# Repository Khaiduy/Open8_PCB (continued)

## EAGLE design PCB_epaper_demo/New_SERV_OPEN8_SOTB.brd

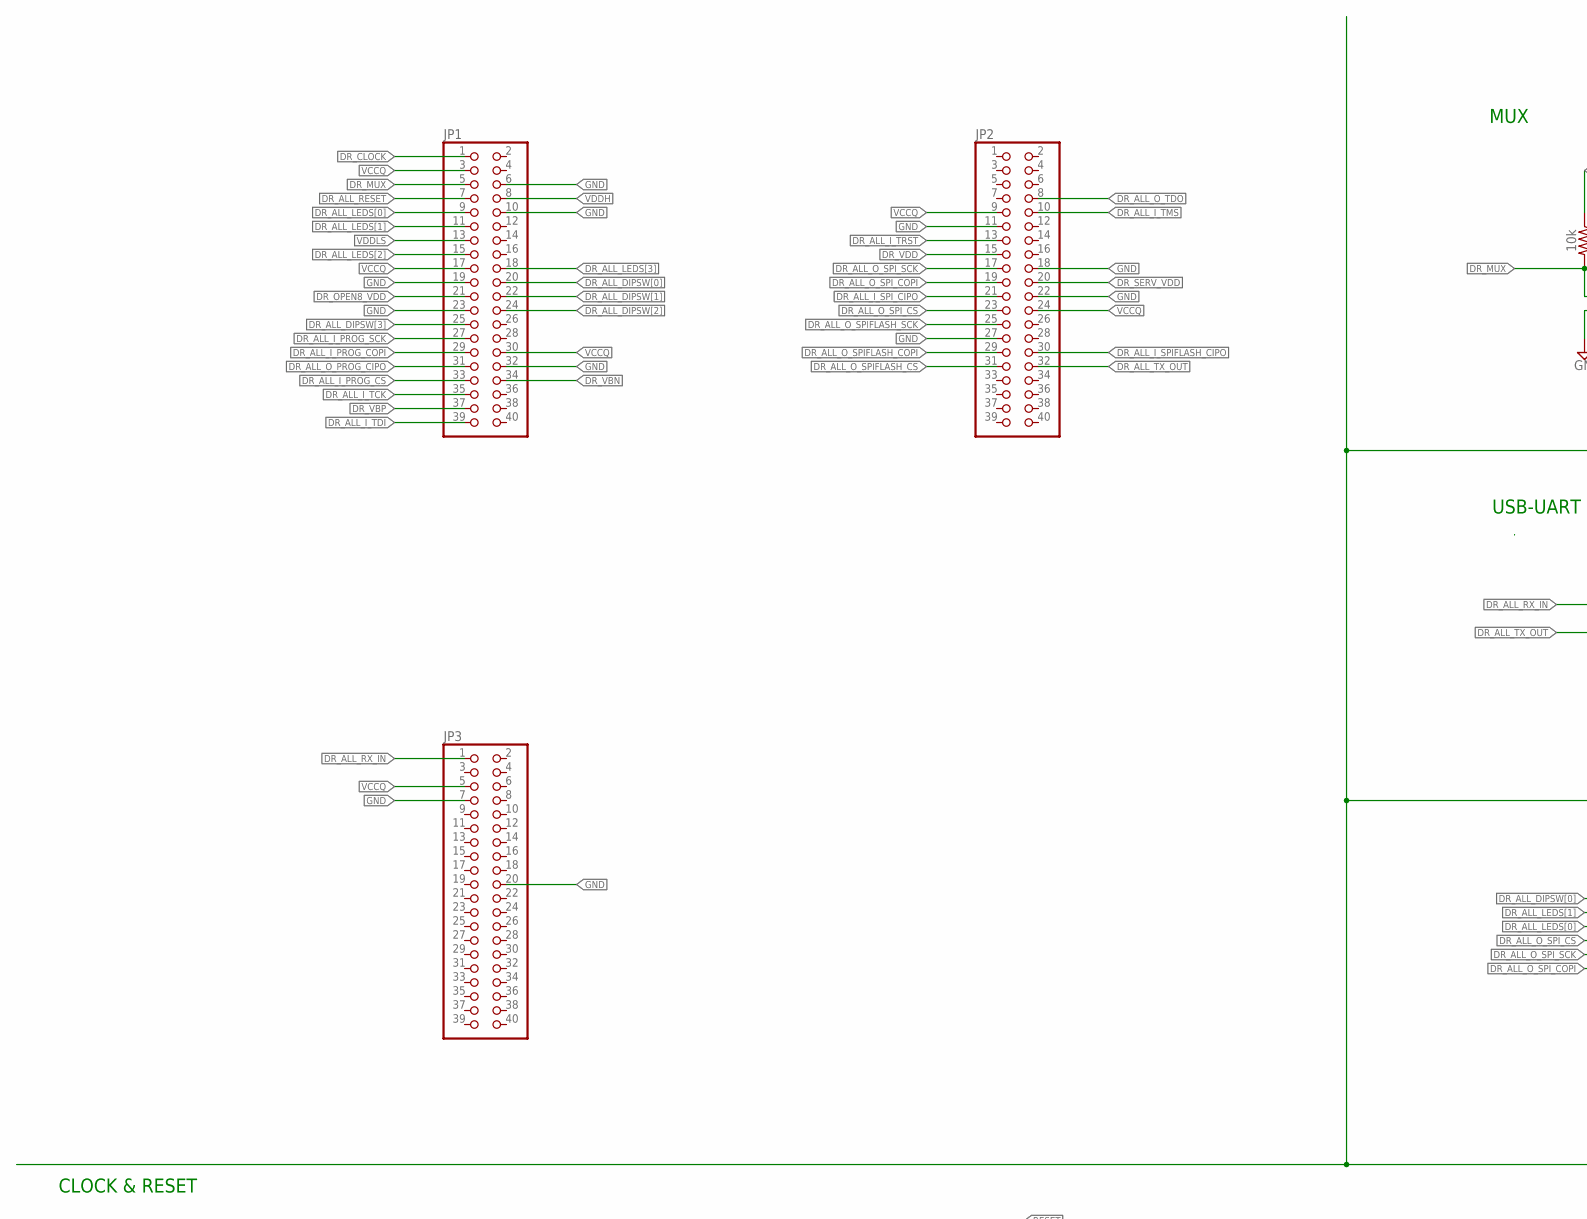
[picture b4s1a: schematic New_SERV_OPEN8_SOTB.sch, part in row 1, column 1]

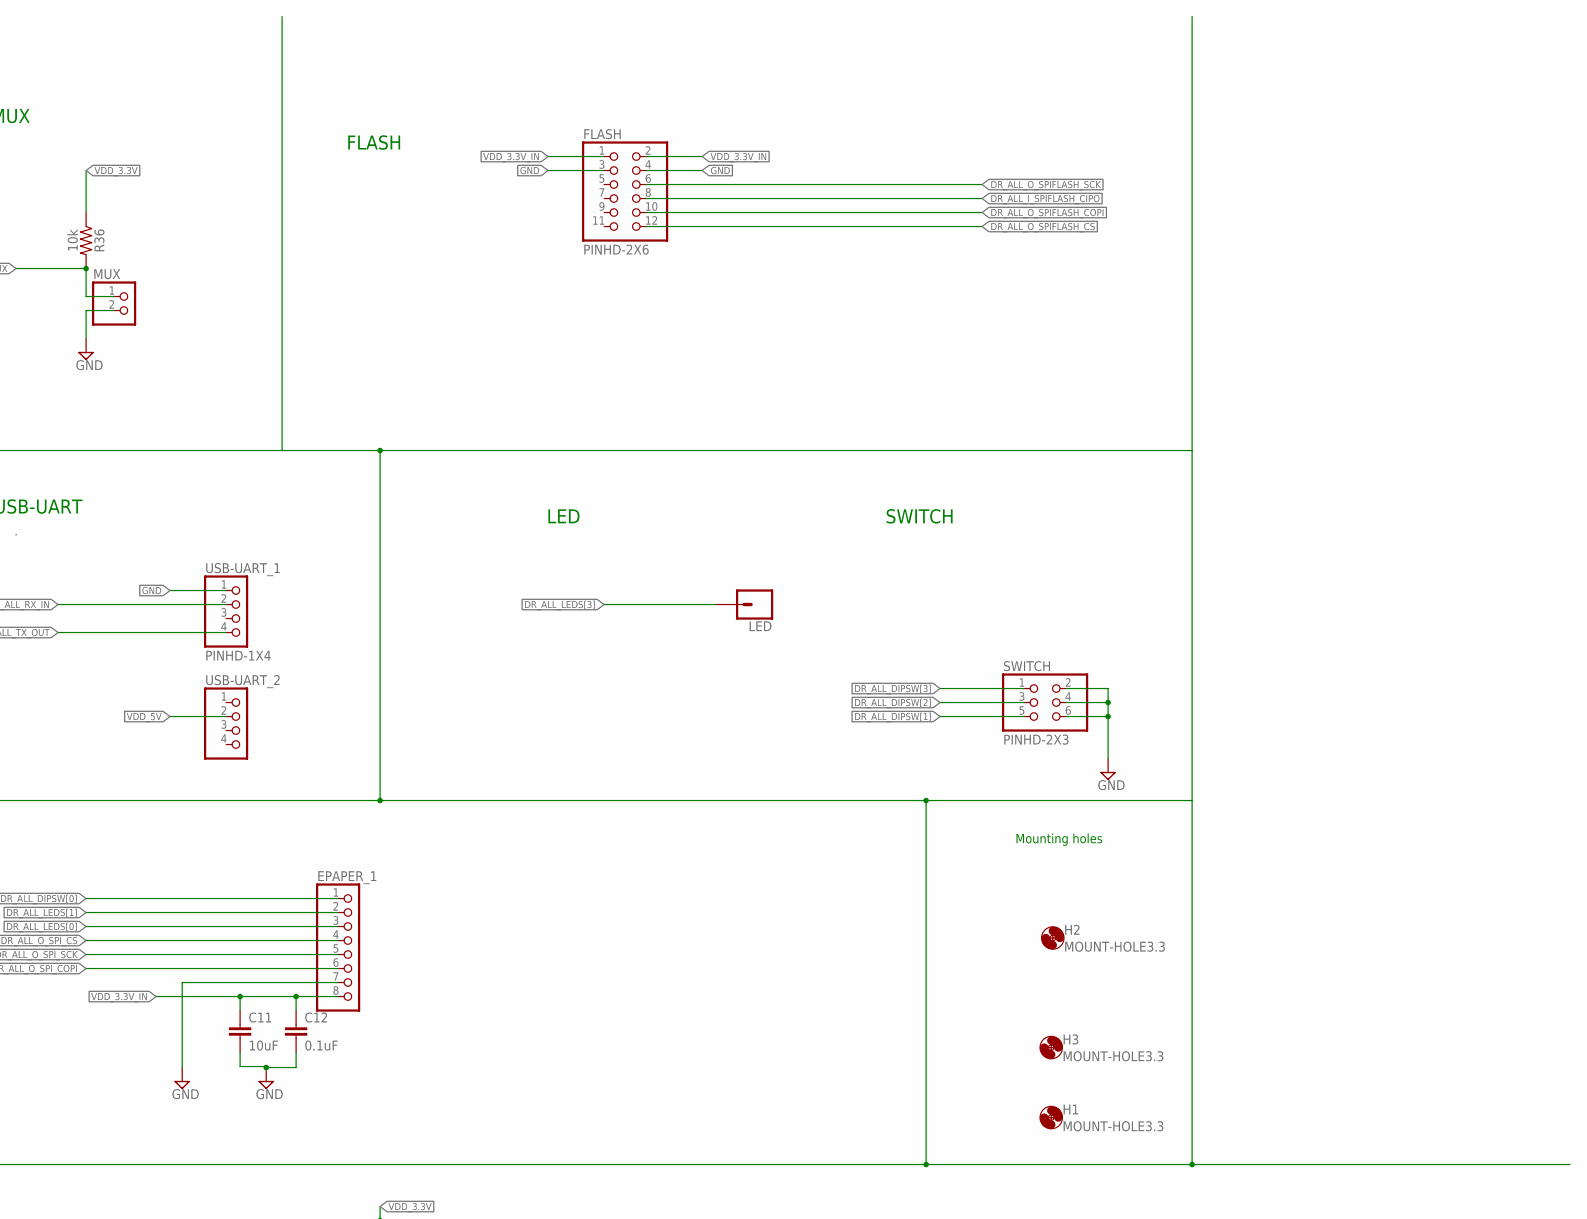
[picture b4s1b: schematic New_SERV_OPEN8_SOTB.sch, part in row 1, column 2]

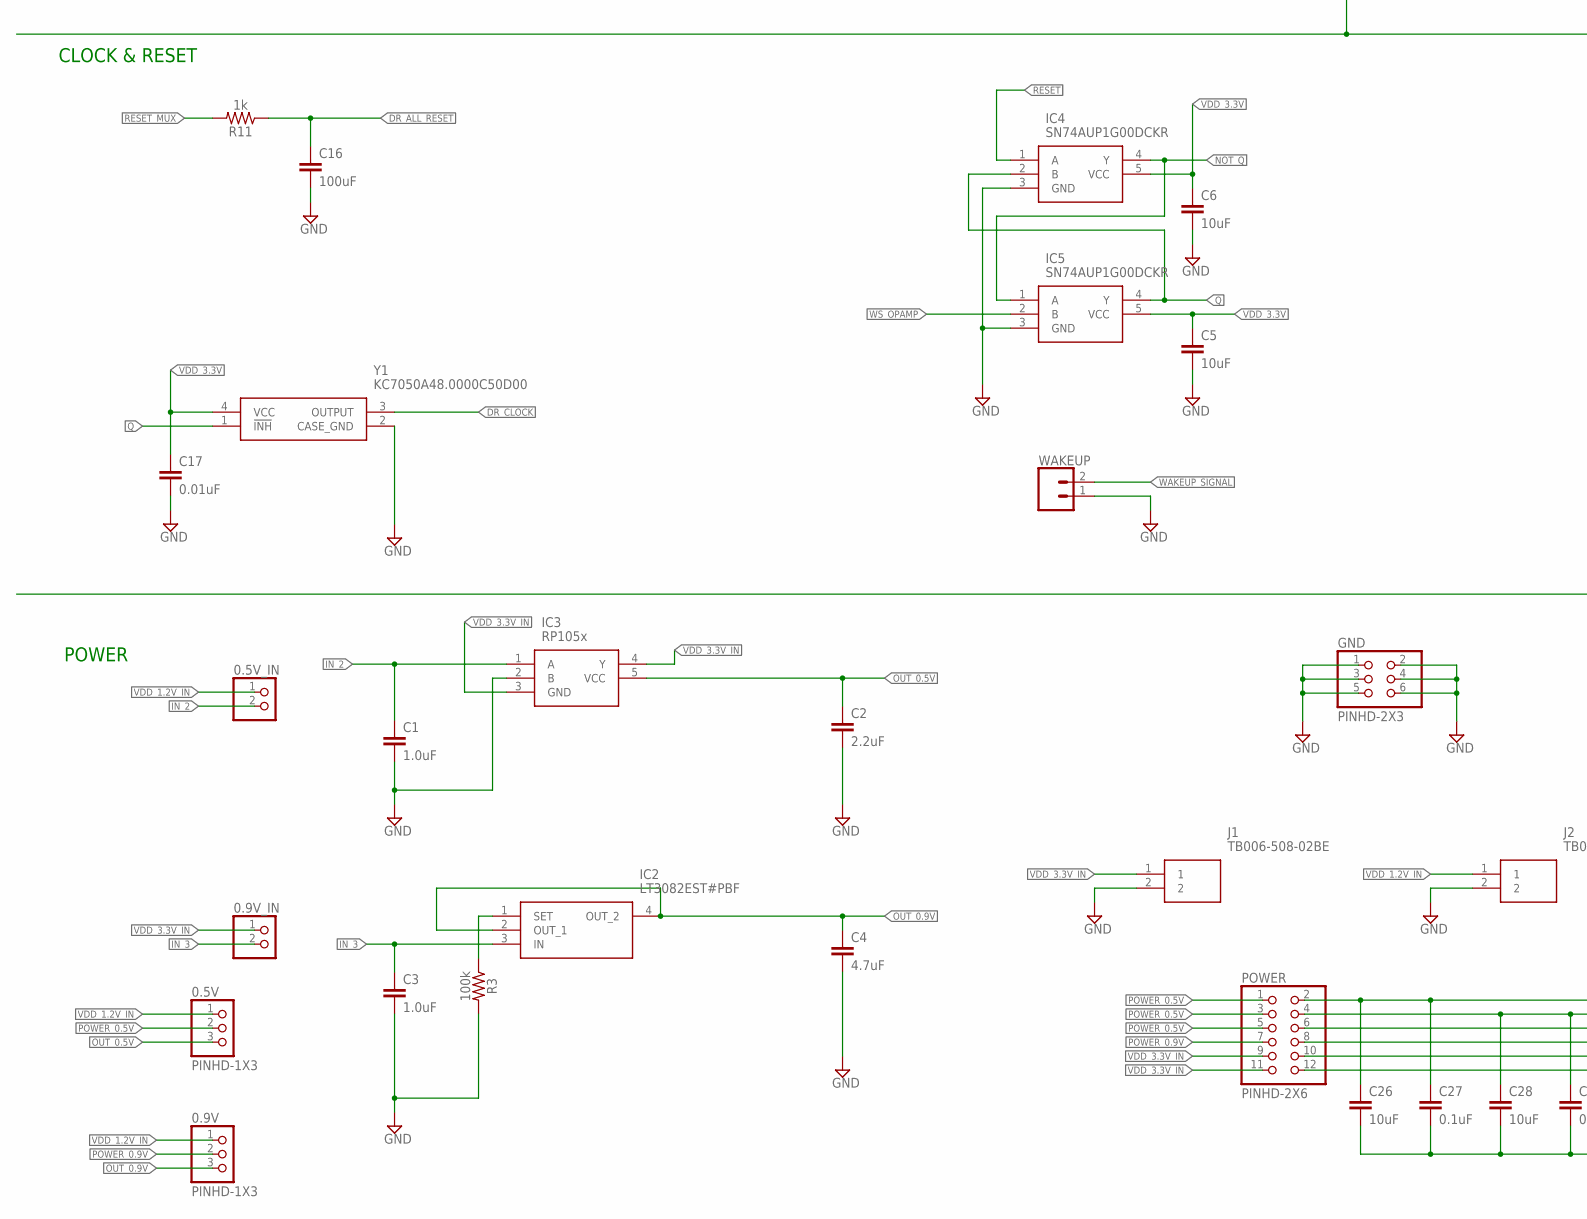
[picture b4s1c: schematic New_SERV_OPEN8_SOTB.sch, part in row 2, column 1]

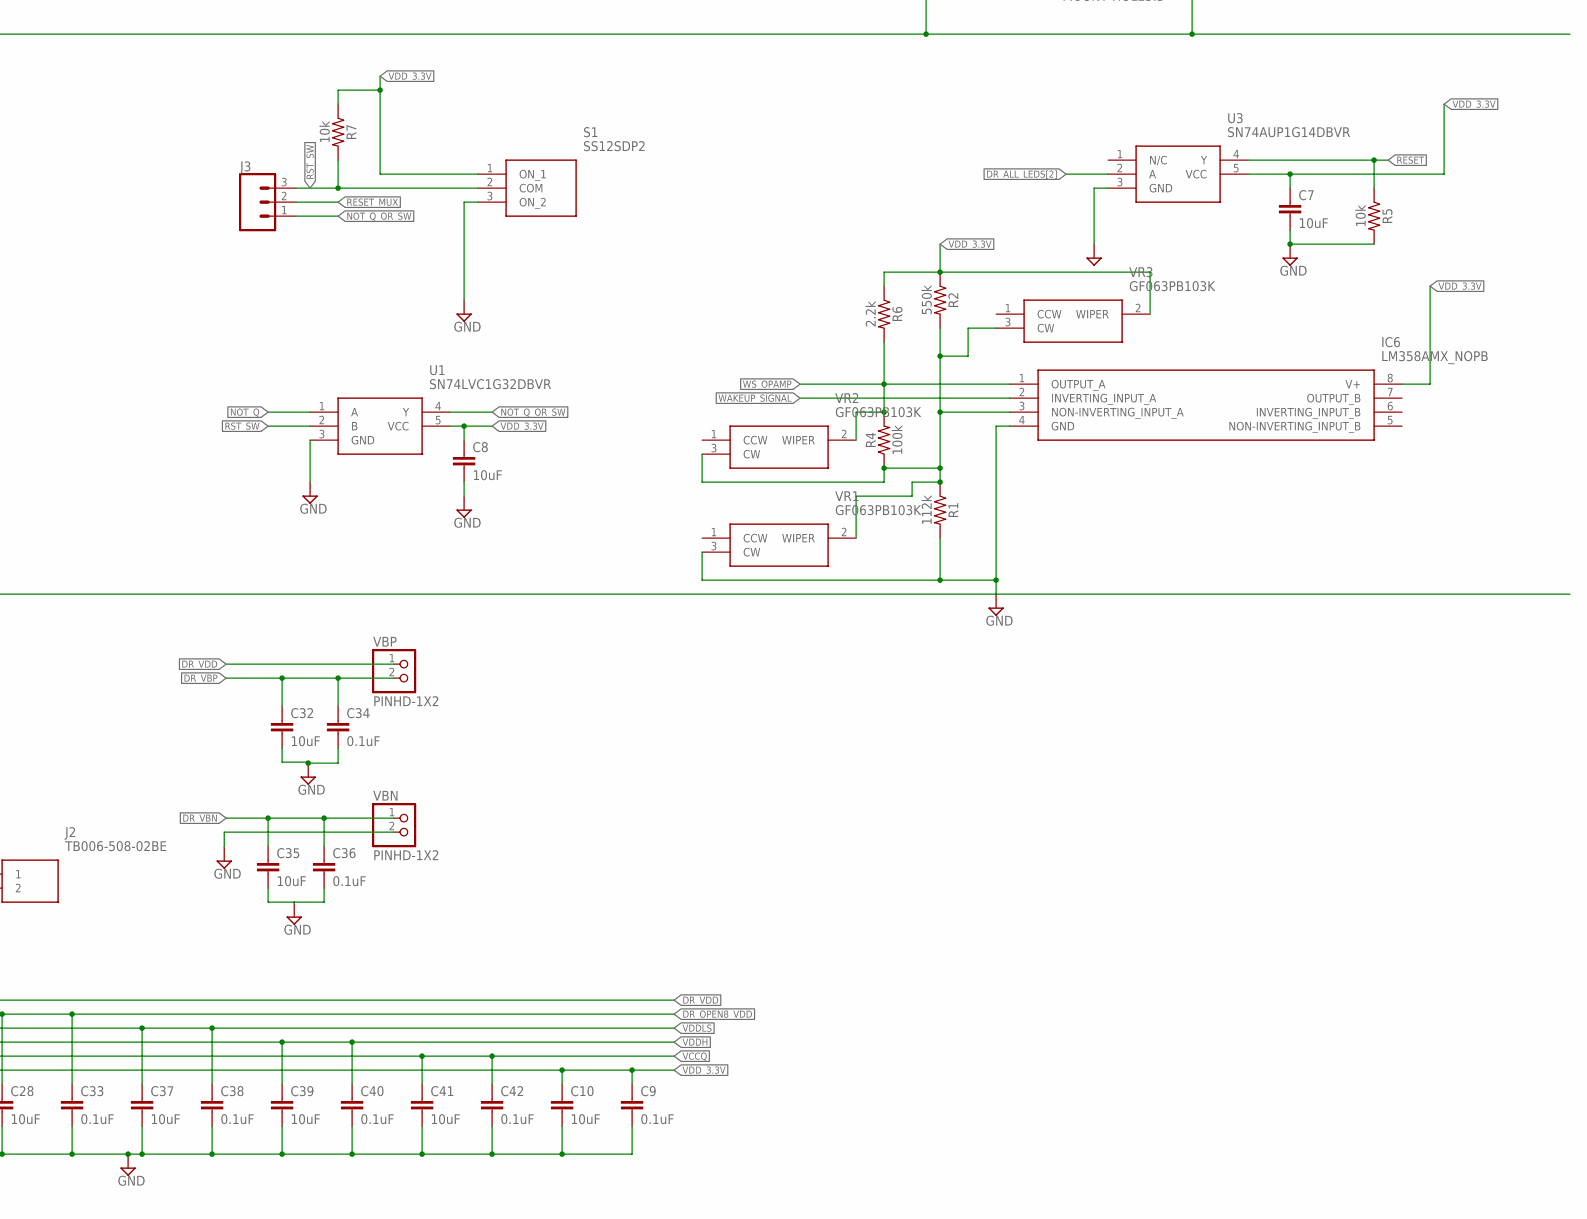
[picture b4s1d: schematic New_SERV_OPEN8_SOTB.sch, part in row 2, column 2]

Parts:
0.5V, 0.9V: PINHD-1X3; 1X03
0.5V_IN, 0.9V_IN: PINHD-1X2; 1X02
C1, C3: 1.0uF; 0805
C2: 2.2uF; 0805
C4: 4.7uF; 0805
C5, C6, C7, C8, C10, C11, C26, C28, C32, C35, C37, C39, C41: 10uF; 0805
C9, C12, C27, C33, C34, C36, C38, C40, C42: 0.1uF; 0805
C16: 100uF; 0805
C17: 0.01uF; 0805
EPAPER_1: PINHD-1X8; 1X08
FLASH: PINHD-2X6; 2X06
GND: PINHD-2X3; 2X03
H1, H2, H3: MOUNT-HOLE3.3; 3,3
IC2: LT3082EST#PBF; SOT230P700X180-4N
IC3: RP105x; SOT95P280X145-5N
IC4, IC5: SN74AUP1G00DCKR; SOT65P210X110-5N
IC6: LM358AMX_NOPB; SOIC127P600X175-8N
J1, J2: TB006-508-02BE; TB00650802BE
J3: CONN_03; 1X03
JP1, JP2, JP3: PINHD-2X20; 2X20
LED: CONN_01; 1X01
MUX: PINHD-1X2; 1X02
POWER: PINHD-2X6; 2X06
R1: 112k; 0805
R2: 550k; 0805
R3, R4: 100k; 0805
R5, R7, R36: 10k; 0805
R6: 2.2k; 0805
R11: 1k; 0805
S1: SS12SDP2
SWITCH: PINHD-2X3; 2X03
U1: SN74LVC1G32DBVR; SOT95P280X145-5N
U3: SN74AUP1G14DBVR; SOT65P210X110-5N
USB-UART_1, USB-UART_2: PINHD-1X4; 1X04
VBN: PINHD-1X2; 1X02
VBP: PINHD-1X2; 1X02
VR1, VR2, VR3: GF063PB103K
WAKEUP: CONN_02; 1X02
Y1: KC7050A48.0000C50D00; KC7050A480000C50D00

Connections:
DR_ALL_DIPSW[0]: EPAPER_1.1, JP1.20
DR_ALL_DIPSW[1]: JP1.22, SWITCH.5
DR_ALL_DIPSW[2]: JP1.24, SWITCH.3
DR_ALL_DIPSW[3]: JP1.25, SWITCH.1
DR_ALL_I_PROG_COPI: JP1.29
DR_ALL_I_PROG_CS: JP1.33
DR_ALL_I_PROG_SCK: JP1.27
DR_ALL_I_SPIFLASH_CIPO: FLASH.8, JP2.30
DR_ALL_I_SPI_CIPO: JP2.21
DR_ALL_I_TCK: JP1.35
DR_ALL_I_TDI: JP1.39
DR_ALL_I_TMS: JP2.10
DR_ALL_I_TRST: JP2.13
DR_ALL_LEDS[0]: EPAPER_1.3, JP1.9
DR_ALL_LEDS[1]: EPAPER_1.2, JP1.11
DR_ALL_LEDS[2]: JP1.15, U3.2 (A)
DR_ALL_LEDS[3]: JP1.18, LED.1
DR_ALL_O_PROG_CIPO: JP1.31
DR_ALL_O_SPIFLASH_COPI: FLASH.10, JP2.29
DR_ALL_O_SPIFLASH_CS: FLASH.12, JP2.31
DR_ALL_O_SPIFLASH_SCK: FLASH.6, JP2.25
DR_ALL_O_SPI_COPI: EPAPER_1.6, JP2.19
DR_ALL_O_SPI_CS: EPAPER_1.4, JP2.23
DR_ALL_O_SPI_SCK: EPAPER_1.5, JP2.17
DR_ALL_O_TDO: JP2.8
DR_ALL_RESET: C16.1, JP1.7, R11.1
DR_ALL_RX_IN: JP3.1, USB-UART_1.2
DR_ALL_TX_OUT: JP2.32, USB-UART_1.4
DR_CLOCK: JP1.1, Y1.3 (OUTPUT)
DR_MUX: JP1.5, MUX.1, R36.2
DR_OPEN8_VDD: C28.1, C33.1, JP1.21, POWER.4
DR_SERV_VDD: JP2.20
DR_VBN: C35.1, C36.1, JP1.34, VBN.1
DR_VBP: C32.1, C34.1, JP1.37, VBP.2
DR_VDD: C26.1, C27.1, JP2.15, POWER.2, VBP.1
GND: C1.2, C2.2, C3.2, C4.2, C5.2, C6.2, C7.2, C8.2, C9.2, C10.2, C11.2, C12.2, C16.2, C17.2, C26.2, C27.2, C28.2, C32.2, C33.2, C34.2, C35.2, C36.2, C37.2, C38.2, C39.2, C40.2, C41.2, C42.2, EPAPER_1.7, FLASH.3, FLASH.4, GND.1, GND.2, GND.3, GND.4, GND.5, GND.6, IC3.2 (B), IC4.3 (GND), IC5.3 (GND), IC6.4 (GND), J1.2, J2.2, JP1.6, JP1.10, JP1.19, JP1.23, JP1.32, JP2.11, JP2.18, JP2.22, JP2.27, JP3.7, JP3.20, MUX.2, R1.2, R3.2, R5.2, S1.3 (ON_2), SWITCH.2, SWITCH.4, SWITCH.6, U1.3 (GND), U3.3 (GND), USB-UART_1.1, VBN.2, VR1.3 (CW), WAKEUP.1, Y1.2 (CASE_GND)
IN_2: 0.5V_IN.2, C1.1, IC3.1 (A)
IN_3: 0.9V_IN.2, C3.1, IC2.3 (IN)
unnamed: IC2.1 (SET), R3.1
unnamed: IC6.3 (NON-INVERTING_INPUT_A), R1.1, R2.2, R4.1, VR1.2 (WIPER), VR2.3 (CW), VR3.3 (CW)
NOT_Q: IC4.4 (Y), IC5.1 (A), U1.1 (A)
NOT_Q_OR_SW: J3.1, U1.4 (Y)
OUT_0.5V: 0.5V.3, C2.1, IC3.5 (VCC)
OUT_0.9V: 0.9V.3, C4.1, IC2.2 (OUT_1), IC2.4 (OUT_2)
POWER_0.5V: 0.5V.2, POWER.1, POWER.3, POWER.5
POWER_0.9V: 0.9V.2, POWER.7
Q: IC4.2 (B), IC5.4 (Y), Y1.1 (!INH)
RESET: IC4.1 (A), R5.1, U3.4 (Y)
RESET_MUX: J3.2, R11.2
RST_SW: J3.3, R7.2, S1.2 (COM), U1.2 (B)
VCCQ: C41.1, C42.1, JP1.3, JP1.17, JP1.30, JP2.9, JP2.24, JP3.5, POWER.10
VDDH: C39.1, C40.1, JP1.8, POWER.8
VDDLS: C37.1, C38.1, JP1.13, POWER.6
VDD_1.2V_IN: 0.5V.1, 0.5V_IN.1, 0.9V.1, J2.1
VDD_3.3V: C5.1, C6.1, C7.1, C8.1, C9.1, C10.1, C17.1, IC4.5 (VCC), IC5.5 (VCC), IC6.8 (V+), POWER.12, R2.1, R6.1, R7.1, R36.1, S1.1 (ON_1), U1.5 (VCC), U3.5 (VCC), VR3.2 (WIPER), Y1.4 (VCC)
VDD_3.3V_IN: 0.9V_IN.1, C11.1, C12.1, EPAPER_1.8, FLASH.1, FLASH.2, IC3.3 (GND), IC3.4 (Y), J1.1, POWER.9, POWER.11
VDD_5V: USB-UART_2.2
WAKEUP_SIGNAL: IC6.2 (INVERTING_INPUT_A), WAKEUP.2
WS_OPAMP: IC5.2 (B), IC6.1 (OUTPUT_A), R4.2, R6.2, VR2.2 (WIPER)

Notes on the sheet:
CLOCK & RESET
Mounting holes
MUX
FLASH
USB-UART
LED
SWITCH
POWER

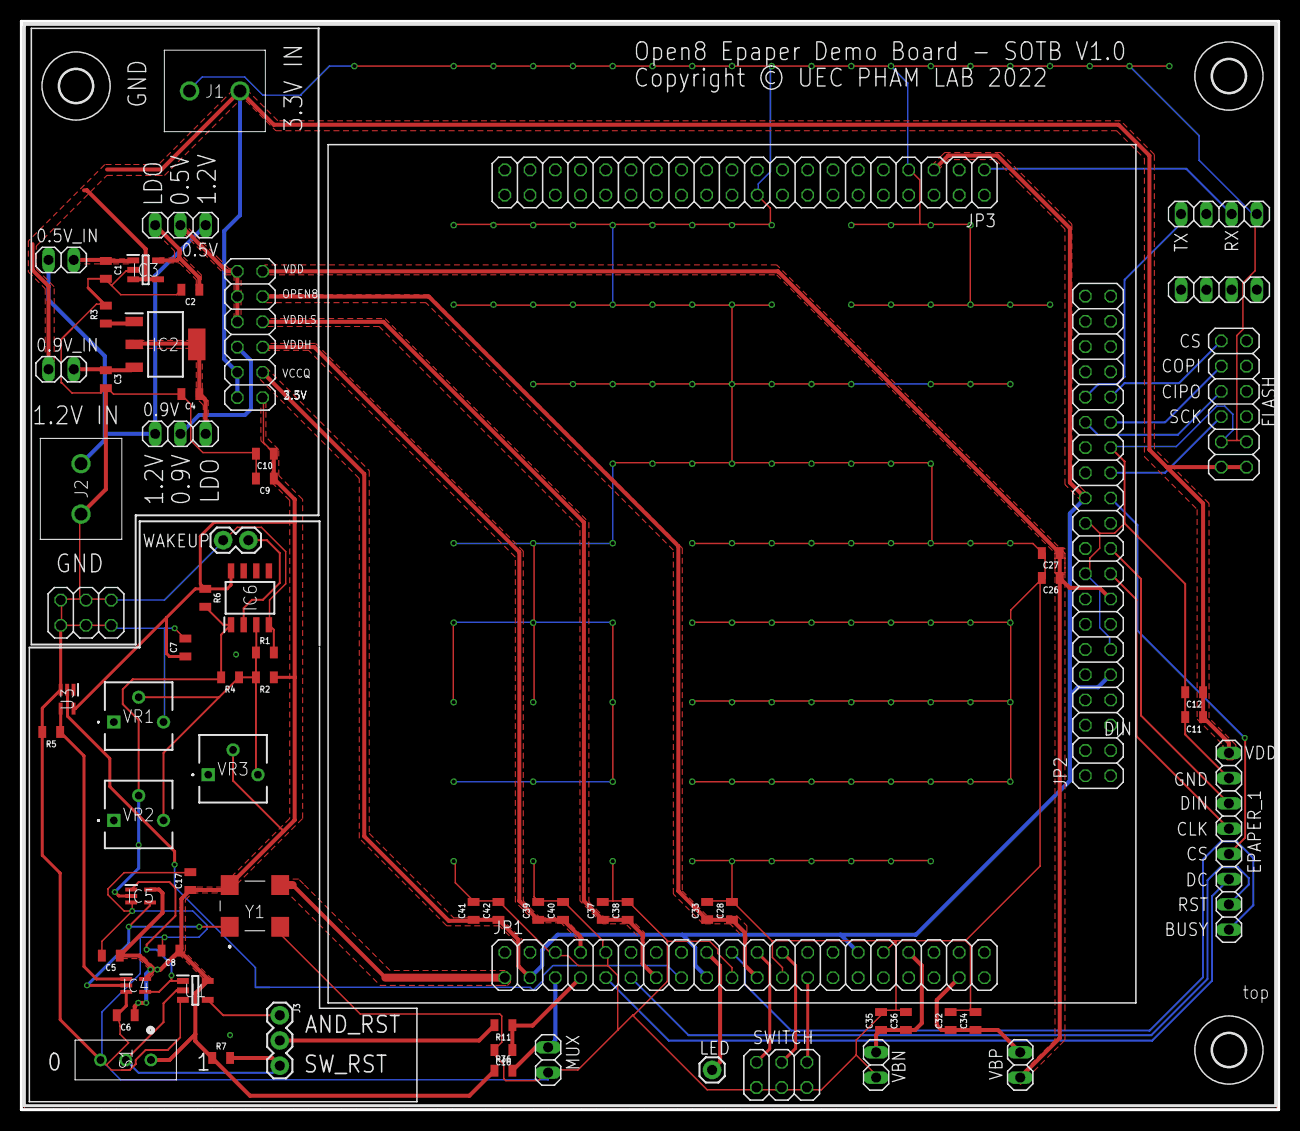
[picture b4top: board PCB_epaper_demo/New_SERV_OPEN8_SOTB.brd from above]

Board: 2 copper layers, 126.5 x 109.5 mm, 74 parts (0 on the bottom side), 47 nets.

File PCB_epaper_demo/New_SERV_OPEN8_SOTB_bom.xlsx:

Comment | Designator | Footprint | LCSC Part #（optional）
0.01uF | C17 | 805 | C1710
0.1uF | C9, C12, C27, C33, C34, C36, C38, C40, C42 | 805 | C49678
1uF | C1, C3 | 805 | C24123
100uF | C16 | 805 | C141660
10uF | C5, C6, C7, C8, C10, C11, C26, C28, C32, C35, C37, C39, C41 | 805 | C17024
2.2uF | C2 | 805 | C87994
4.7uF | C4 | 805 | C92762
100k | R4, R3 | 805 | C149504
10k | R5, R7, R36 | 805 | C17414
560k | R2 | 805 | C352198
SN74AUP1G00DCKR | IC4, IC5 | SC-70-5 | C206053
SN74AUP1G14DBVR | U3 | SOT-23-5 | C2682131
SN74LVC1G32DBVR | U1 | SOT-23-5 | C10096
LM358AMX_NOPB | IC6 | SOIC-8 | C5423
1k | R11 | 805 | C17513
2.2k | R6 | 805 | C17520
110k | R1 | 805 | C413317
